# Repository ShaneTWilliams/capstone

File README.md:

# capstone

## Setup

First, clone submodules with:

```
git submodule update --init
cd software/firmware/lib/pico-sdk
git submodule update --init
```

You don't *have* to, but using a `venv` for the following steps is a good idea. To create one, run:

```
cd software
python -m venv .csvenv
```

Then to activate it, run the following. You'll need to do this each time you open a new shell, but you can put it in your shell's dotfile to automate this.

```
Bash:                   source .csvenv/bin/activate
Csh:                    source .csvenv/bin/activate.csh
Fish:                   source .csvenv/bin/activate.fish
Windows CMD:            .csvenv\Scripts\activate.bat
Windows PowerShell:     .csvenv\Scripts\Activate.ps1
```

### Windows

Open PowerShell as an administrator and install chocolatey using [these instructions](https://chocolatey.org/install#individual).

Still using an administrator shell, install dependencies with:

```
choco install make cmake mingw gcc-arm-embedded protoc python --installargs '"ADD_CMAKE_TO_PATH=User"'
```

In a non-administrator PowerShell, install the Python package with:

```
cd software
pip install -e . --user
```

If you get warnings about the scripts directory not being on your PATH, add it by typing `env` in the Windows search bar and click on "Edit the system environment variables". Next, on the `Advanced` tab, click `Environment Variables`. Under `User Variables`, find `Path`, click on it, select `Edit`, then click `New`. Type in the directory that Pip warned about, and exit.

Close and reopen your PowerShell window.

### Linux

Install dependencies with the following command:

```
sudo apt install cmake protobuf-compiler pnpm
```

Install the [GNU ARM embedded toolchain](https://developer.arm.com/downloads/-/arm-gnu-toolchain-downloads) manually.

Install the Python package with:

```
cd software
pip install -e .
```

If you get warnings about the scripts directory not being on your PATH, add it adding the following line to your shell's `rc` dotfile.

```
export PATH=$PATH:<scripts dir here>
```

### MacOS

Install dependencies with the following command:

```
brew install make cmake protobuf gcc-arm-embedded pnpm
```

Install the Python package with:

```
cd software
pip install -e .
```

If you get warnings about the scripts directory not being on your PATH, add it adding the following line to your shell's `rc` dotfile.

```
export PATH=$PATH:<scripts dir here>
```

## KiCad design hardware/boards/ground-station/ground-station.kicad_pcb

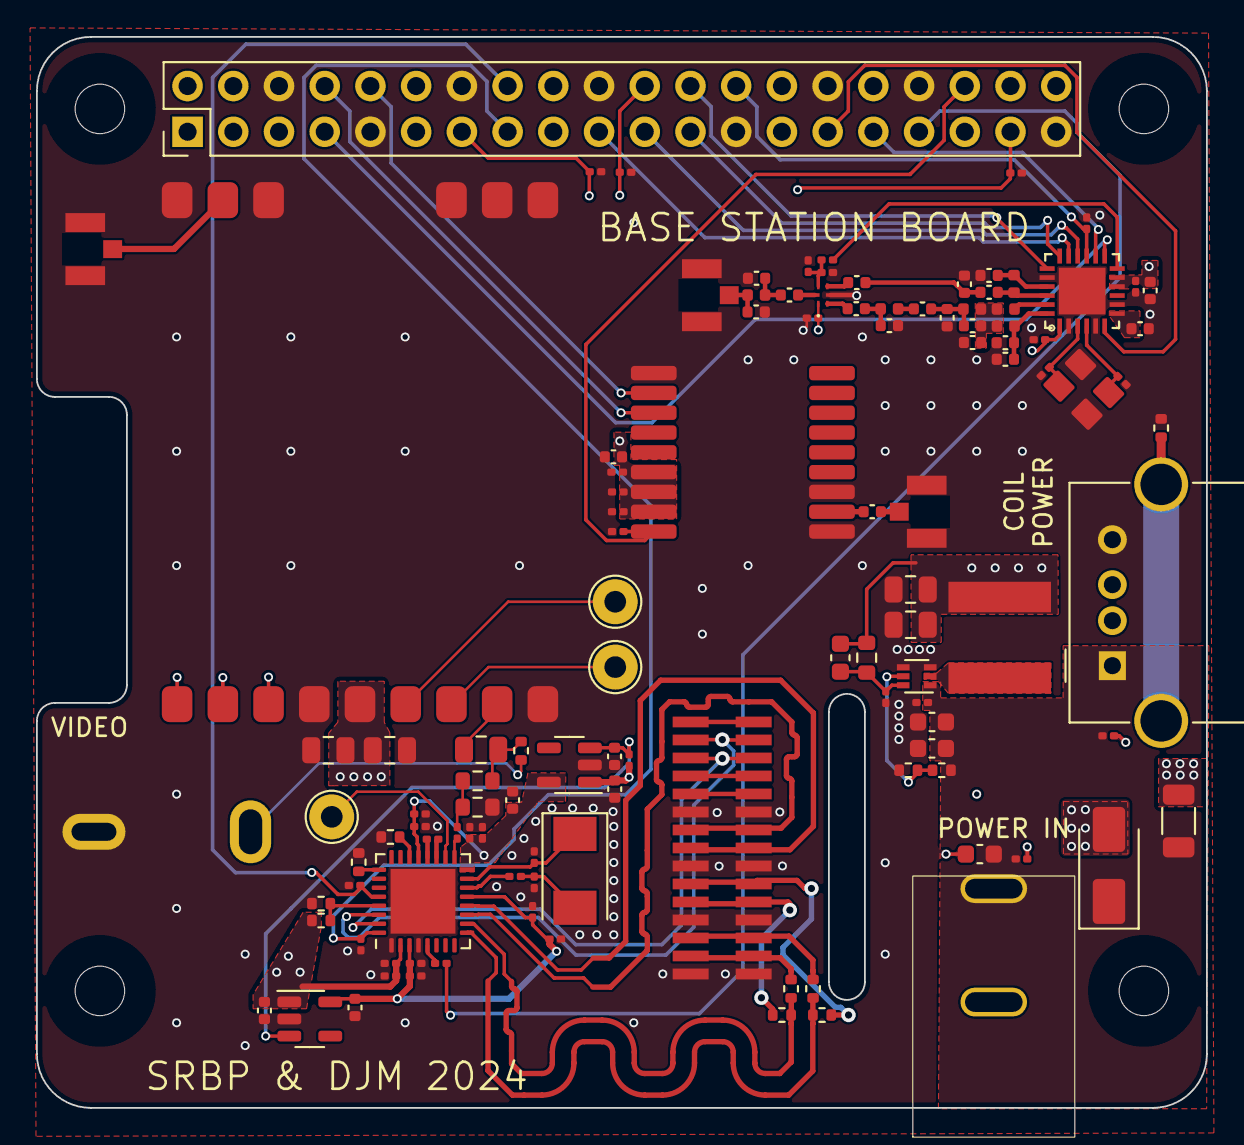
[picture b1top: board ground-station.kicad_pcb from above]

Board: 4 copper layers, 65.0 x 59.5 mm, 117 parts (0 on the bottom side), 77 nets.

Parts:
C1, C3, C24, C27, C205, C206, C207, C210, C231, C604, C611, C614, C615, C618, C620: 100n; C_0201_0603Metric
C2: C_0603_1608Metric
C23, C25, C26: 10u; C_0603_1608Metric
C33, C34, C201, C202, C203: 22u; C_0805_2012Metric
C204: 470n; C_0402_1005Metric
C208: 2.2u; C_0402_1005Metric
C209, C215: 47p; C_0402_1005Metric
C211, C605, C606, C607, C608: 1u; C_0402_1005Metric
C212, C214: 16p; C_0201_0603Metric
C213: 47n; C_0402_1005Metric
C216, C223: 1.8p; C_0402_1005Metric
C217: 2.4p; C_0402_1005Metric
C218, C224, C225: 1n; C_0402_1005Metric
C219, C221: 5.6p; C_0402_1005Metric
C220: 3p; C_0402_1005Metric
C222, C228: 39p; C_0402_1005Metric
C226: 100p; C_0201_0603Metric
C227, C612, C613, C616, C617, C619: 10n; C_0201_0603Metric
C229, C230: 3.3p; C_0402_1005Metric
C602, C603: 22p; C_0201_0603Metric
C610: 680n; C_0402_1005Metric
D401: SMAJ5.0A; D_SMA
J1: USB_A; USB_A_Molex_67643_Horizontal
J2: Barrel_Jack; PJ-037A
J3: Conn_Coaxial; RCJ-054
J101: Raspberry_Pi_2_3; PinHeader_2x20_P2.54mm_Vertical
J102: Conn_01x15; FFC3A20-15-G
J201, J202, J203: U.FL; U.FL-R-SMT-1(60)
L4: 1.5u; FNR6028S1R5MT
L201: 0R; L_0402_1005Metric
L202: 47n; L_0402_1005Metric
L203: 15n; L_0402_1005Metric
L204: 2.5n; L_0402_1005Metric
L205: 4.7n; L_0402_1005Metric
L206: 9.1n; L_0402_1005Metric
R1, R2, R6, R22, R23, R24, R25, R26, R27, R28, R208: 0; R_0402_1005Metric
R3: 0; R_1206_3216Metric
R4: 24R; R_0603_1608Metric
R5: 51R; R_0603_1608Metric
R7: 100k; R_0402_1005Metric
R8: 135k; R_0603_1608Metric
R9: 30k; R_0201_0603Metric
R201, R205, R604, R605: 100k; R_0201_0603Metric
R202, R203, R204, R606: 10k; R_0201_0603Metric
R206: 2.2k; R_0201_0603Metric
R207: 2.7k; R_0201_0603Metric
R301: 47R; R_0201_0603Metric
R603: 1k; R_0201_0603Metric
TP1, TP2, TP3: TestPoint; TestPoint_THTPad_D2.5mm_Drill1.2mm
U3: TPS564242DRLR; SOT-563
U201: SX1262IMLTRT
U202: RX5808
U203: SW-GPS01
U204: SKY13453-385LF; IC_SKY13453-385LF
U601: ADV7282A-M; QFN-32-1EP_5x5mm_P0.5mm_EP3.6x3.6mm
U602, U603: AP2127K-1.8; SOT-23-5
Y201: 32 MHz; JYJE-3TJ432000HYFBC
Y601: 28.63636 MHz; Crystal_SMD_Abracon_ABM3-2Pin_5.0x3.2mm

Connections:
+3V3: C2.2, C33.1, C34.1, C205.1, C206.1, C207.1, C208.1, C210.1, C211.1, C227.1, C231.1, C605.1, C606.1, C611.1, C612.1, L4.2, R8.1, R27.1, R606.1, U201.1 (VDD_IN), U201.10 (VBAT), U201.11 (VBAT_IO), U203.6 (V_BCKP), U203.7 (VCC_IO), U203.8 (VCC), U204.1 (VDD), U601.2 (DVDDIO), U602.1 (VIN), U603.1 (VIN)
+5V: C1.1, C23.1, C24.1, C25.1, C26.1, C27.1, C201.1, C202.1, D401.1 (A1), J1.1 (VBUS), J2.1, R2.1, R3.1, U3.1 (VIN), U202.5 (VCC)
/CAM_CK_N: J102.8, U601.12 (CLKN)
/CAM_CK_P: J102.9, U601.11 (CLKP)
/CAM_D0_CONN_N: J102.2, R25.2
/CAM_D0_CONN_P: J102.3, R26.2
/CAM_D0_N: R23.1, R25.1, U601.10 (D0N)
/CAM_D0_P: R24.1, R26.1, U601.9 (D0P)
/CAM_D1_CONN_N: J102.5, R23.2
/CAM_D1_CONN_P: J102.6, R24.2
/CAM_SCL: J102.13, U601.31 (SCLK)
/CAM_SDA: J102.14, U601.30 (SDATA)
/DIGITAL_RADIO_BUSY: J101.31 (GCLK2/GPIO6), U201.14 (BUSY)
/DIGITAL_RADIO_DIO1: J101.7 (GCLK0/GPIO4), U201.13 (DIO1)
/DIGITAL_RADIO_DIO3: J101.29 (GCLK1/GPIO5), U201.6 (DIO3)
/DIGITAL_RADIO_MISO: J101.21 (MISO0/GPIO9), U201.16 (MISO)
/DIGITAL_RADIO_MOSI: J101.19 (MOSI0/GPIO10), U201.17 (MOSI)
/DIGITAL_RADIO_SCLK: J101.23 (SCLK0/GPIO11), U201.18 (SCK)
/GPS_UART_RX: J101.8 (GPIO14/TXD), U203.3 (RXD)
/GPS_UART_TX: J101.10 (GPIO15/RXD), U203.2 (TXD)
/Radios/DIO2: R206.1, U201.12 (DIO2)
/Radios/SW_RX: C217.1, C218.2, C225.2
/Radios/SW_TX: C223.2, C224.2, L205.2
/Radios/VIDEO_OUT: C203.2, R4.1, R208.1
/Radios/XTAL_A: C214.1, U201.3 (XTA), Y201.1
/Radios/XTAL_B: C212.1, U201.4 (XTB), Y201.3
/VIDEO_CH1: J101.22 (GPIO25), R202.1, U202.9 (CH1)
/VIDEO_CH2: J101.37 (GPIO26), R203.1, U202.8 (CH2)
/VIDEO_CH3: J101.13 (GPIO27), R204.1, U202.7 (CH3)
/Video Digitizer/DIGITIZER_ANALOG_SUPPLY: C607.1, C617.1, C618.1, C619.1, C620.1, U601.16 (PVDD), U601.21 (AVDD), U603.5 (VOUT)
/Video Digitizer/DIGITIZER_DIGITAL_SUPPLY: C608.1, C613.1, C614.1, C615.1, C616.1, U601.3 (DVDD), U601.13 (MVDD), U602.5 (VOUT)
/Video Digitizer/VID_EN_1V8: C610.1, R606.2, U602.3 (EN), U603.3 (EN)
/~DIGITAL_RADIO_RESET: J101.26 (~CE1/GPIO7), R201.1, U201.15 (~NRESET)
/~DIGITAL_RADIO_nCS: J101.24 (~CE0/GPIO8), U201.19 (NSS)
/~DIGITIZER_INTRQ: J101.33 (PWM1/GPIO13), R301.2
/~DIGITIZER_PWRDWN: J101.15 (GPIO22), R604.1, U601.32 (~PWRDWN)
/~DIGITIZER_RESET: J101.16 (GPIO23), R605.1, U601.28 (~RESET)
/~GPS_RESET: J101.36 (GPIO16), R205.1, U203.9 (~RESET)
GND: C1.2, C23.2, C24.2, C25.2, C26.2, C27.2, C33.2, C34.2, C201.2, C202.2, C204.2, C205.2, C206.2, C207.2, C208.2, C210.2, C211.2, C212.2, C213.2, C214.2, C215.2, C216.2, C218.1, C219.2, C221.1, C223.1, C226.1, C227.2, C229.1, C230.1, C231.2, C602.1, C603.1, C605.2, C606.2, C607.2, C608.2, C610.2, C611.2, C612.2, C613.2, C614.2, C615.2, C616.2, C617.2, C618.2, C619.2, C620.2, D401.2 (A2), J1.4 (GND), J2.2, J3.2 (Ext), J101.6 (GND), J101.9 (GND), J101.14 (GND), J101.20 (GND), J101.25 (GND), J101.30 (GND), J101.34 (GND), J101.39 (GND), J102.1, J102.4, J102.7, J102.10, J201.2 (Ext), J202.2 (Ext), J203.2 (Ext), R1.2, R5.2, R6.1, R7.2, R9.2, R22.1, R28.1, R201.2, R202.2, R203.2, R204.2, R205.2, R207.1, R604.2, R605.2, U3.3 (GND), U3.4 (AGND), U201.2 (GND), U201.5 (GND), U201.8 (GND), U201.20 (GND), U201.25 (EXP), U202.1 (GND), U202.6 (GND), U202.10 (GND), U202.12 (GND), U202.13 (GND), U202.14 (GND), U202.15 (GND), U203.1 (GND), U203.10 (GND), U203.12 (GND), U204.3 (GND), U601.1 (DGND), U601.4 (DGND), U601.33 (EPAD), U602.2 (GND), U603.2 (GND), Y201.2, Y201.4
unnamed: C3.1, R4.2, R5.1
unnamed: C219.1, C220.1, L201.1, L202.1, L204.1
unnamed: C220.2, C221.2, C222.2, L204.2
unnamed: C222.1, L205.1
unnamed: C228.1, C229.2, L206.1
unnamed: C603.2, R603.1, Y601.2
unnamed: J1.5 (Shield), R1.1
unnamed: J3.1 (In), R208.2
unnamed: J101.2 (5V), J101.4 (5V), R3.2
unnamed: J201.1 (In), U202.11 (RFIN)
unnamed: C209.2, J202.1 (In)
unnamed: C230.2, J203.1 (In), L206.2
unnamed: R2.2, R7.1, U3.5 (EN)
unnamed: C2.1, R8.2, R9.1, U3.6 (FB)
unnamed: L4.1, U3.2 (SW)
unnamed: C217.2, L203.1, U201.22 (RFI_N)
unnamed: C216.1, L203.2, U201.21 (RFI_P)
unnamed: L201.2, U201.23 (RFO)
unnamed: C204.1, U201.7 (VREG)
unnamed: C213.1, C215.1, L202.2, U201.24 (VR_PA)
unnamed: TP2.1, U202.3 (AUDIO)
unnamed: TP1.1, U202.4 (RSSI)
unnamed: C203.1, U202.2 (VIDEO)
unnamed: C209.1, U203.11 (RF_IN)
unnamed: C224.1, U204.2 (RF1)
unnamed: C225.1, U204.4 (RF2)
unnamed: C228.2, U204.6 (RFC)
unnamed: C226.2, R206.2, R207.2, U204.5 (VTCL)
unnamed: C3.2, U601.17 (AIN1)
unnamed: TP3.1, U601.18 (AIN2)
unnamed: R27.2, R28.2, U601.29 (ALSB)
unnamed: R6.2, U601.22 (DIAG1)
unnamed: R22.2, U601.25 (DIAG2)
unnamed: C604.2, U601.20 (VREFN)
unnamed: C604.1, U601.19 (VREFP)
unnamed: C602.2, U601.15 (XTALN), Y601.1
unnamed: R603.2, U601.14 (XTALP)
unnamed: R301.1, U601.5 (~INTRQ)

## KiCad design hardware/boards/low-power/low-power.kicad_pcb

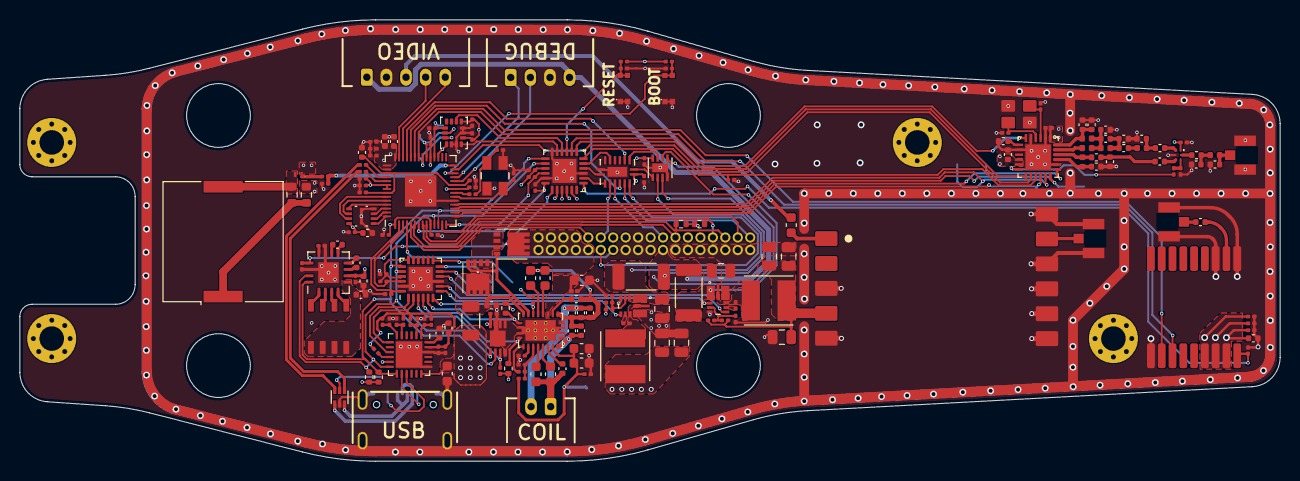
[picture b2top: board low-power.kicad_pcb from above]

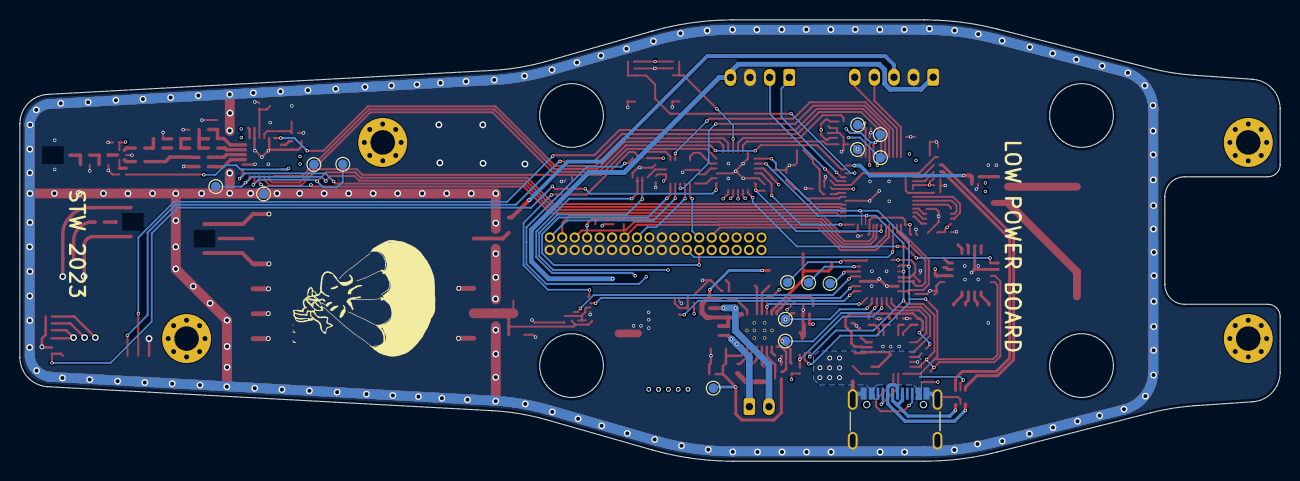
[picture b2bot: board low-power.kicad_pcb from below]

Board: 4 copper layers, 128.5 x 45.0 mm, 201 parts (18 on the bottom side), 156 nets.

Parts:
BZ801: Murata PKLCS; Buzzer_Murata_PKLCS1212E
C201, C202, C205, C209, C402, C502, C503, C504, C505, C506, C507, C510, C511, C512, C513, C514, C515, C517, C601, C602, C606, C607, C701, C702, C805, C806, C903, C904, C911, C1006: 100n; C_0201_0603Metric
C203, C501, C508, C509, C516, C804: 2.2u; C_0402_1005Metric
C204, C407: 47p; C_0402_1005Metric
C206, C207: 33nF; C_0402_1005Metric
C208: 68nF; C_0402_1005Metric
C210: 130p; C_0402_1005Metric
C211: 1uF; C_0402_1005Metric
C212: 1.8n; C_0402_1005Metric
C213, C218: 0.47uF; C_0603_1608Metric
C214, C217: 47nF; C_0603_1608Metric
C215, C216: 10nF; C_0402_1005Metric
C219, C220: 0.1uF; C_0201_0603Metric
C221, C222, C223: 10uF; C_0603_1608Metric
C301: 22u; C_0603_1608Metric
C302, C907, C908, C909, C910: 22u; C_0805_2012Metric
C401: 470n; C_0402_1005Metric
C403, C604, C605, C801, C802, C803: 1u; C_0402_1005Metric
C404, C406: 16p; C_0201_0603Metric
C405: 47n; C_0402_1005Metric
C408, C415: 1.8p; C_0402_1005Metric
C409: 2.4p; C_0402_1005Metric
C410, C416, C417: 1n; C_0402_1005Metric
C411, C413: 5.6p; C_0402_1005Metric
C412: 3p; C_0402_1005Metric
C414, C420: 39p; C_0402_1005Metric
C418: 1n; C_0201_0603Metric
C419: 10n; C_0201_0603Metric
C421, C422: 3.3p; C_0402_1005Metric
C518, C519: 30p; C_0201_0603Metric
C603: 1u; C_0603_1608Metric
C901, C902: 10u; C_0805_2012Metric
C905: 33p; C_0201_0603Metric
C906: 47p; C_0201_0603Metric
D601: USBLC6-2P6; SOT50P160X60-6N
D801: TC5050RGBW
H101, H102, H103, H104: MountingHole_Pad; MountingHole_2.5mm_Pad_Via
J101: Conn_01x05_Pin; JST_PH_S5B-PH-K_1x05_P2.00mm_Horizontal
J102: Conn_02x18_Top_Bottom; 20021311-00036T4LF
J103: Conn_01x04; JST_PH_S4B-PH-K_1x04_P2.00mm_Horizontal
J201, J301, J401: U.FL; U.FL-R-SMT-1(60)
J601: USB_C_Receptacle_USB2.0; USB_C_Receptacle_G-Switch_GT-USB-7010ASV
L201: TDK WR483265-15F5-G; JST_PH_S2B-PH-K_1x02_P2.00mm_Horizontal
L402: 0R; L_0402_1005Metric
L403: 47n; L_0402_1005Metric
L404: 15n; L_0402_1005Metric
L405: 2.5n; L_0402_1005Metric
L406: 4.7n; L_0402_1005Metric
L407: 9.1n; L_0402_1005Metric
L901: 4.7u; IND_LQH5BPN6R8NT0L
L902: 6.8u; IND_LQH5BPN6R8NT0L
Q201, Q202: DMP3013SFV; DMP3013SFV7
Q801: DMN2400UFB4; TRXDFN100X60X40-3N
R201, R401, R701, R801, R803: 100k; R_0201_0603Metric
R202, R206, R210, R501, R601, R602, R603, R1010, R1011: 10k; R_0201_0603Metric
R203: 0R; R_1206_3216Metric
R204: 66R; R_0201_0603Metric
R205: 196R; R_0201_0603Metric
R207, R208: 10k; R_0402_1005Metric
R209: 20k; R_0201_0603Metric
R402, R505: 100R; R_0201_0603Metric
R502, R503: 27R; R_0201_0603Metric
R504, R506, R507, R508: 4.7k; R_0402_1005Metric
R604: 4.7k; R_0201_0603Metric
R605, R606, R609, R610, R611, R612: 0R; R_0201_0603Metric
R607, R608: 5.1k; R_0201_0603Metric
R802: 7.5k; R_0201_0603Metric
R804: 1k; R_0201_0603Metric
R805: 330R; R_0603_1608Metric
R806: 1k; R_0603_1608Metric
R901, R902: 10m 1/2W; R_2010_5025Metric
R903: 91k; R_0201_0603Metric
R904, R906: 30k; R_0201_0603Metric
R905: 157k; R_0201_0603Metric
SW501, SW601: SW_Push; R-668048
TP202, TP203, TP204, TP505, TP506, TP507, TP508, TP509, TP510, TP511, TP512, TP1101, TP1102, TP1104: TestPoint; TestPoint_Pad_D1.0mm
U201: SW-GPS01
U202: LM75BTP,147
U203: BQ51013B; IC_MSP430FR2522IRHLR
U301: TX5813
U401: SX1262IMLTRT
U402: SKY13453-385LF; IC_SKY13453-385LF
U501: W25Q16JVUXIQ; IC_W25Q16JVUXIQ_TR
U502: RP2040; QFN-56-1EP_7x7mm_P0.4mm_EP3.2x3.2mm
U601, U1002: TCA9539RTWR; WQFN-24-1EP_4x4mm_P0.5mm_EP2.45x2.45mm
U602: TMUX1309BQBR; QFN50P350X250X80-17N
U603: CYPD3177; QFN-24-1EP_4x4mm_P0.5mm_EP2.7x2.7mm
U701: LSM6DSM; LGA-14_3x2.5mm_P0.5mm_LayoutBorder3x4y
U801: IS31FL3197; QFN-16-1EP_4x4mm_P0.65mm_EP2.1x2.1mm
U901, U902: AP63356QZV-7; CONV_AP63356QZV-7
U903: INA2180A3IDSGR; SON50P200X200X80-9N
Y401: 32 MHz; JYJE-3TJ432000HYFBC
Y501: 12 MHz; SMD_2MSB4SI_YXC

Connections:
+1V1: C502.1, C506.1, C509.1, U502.23 (DVDD), U502.45 (VREG_VOUT), U502.50 (DVDD)
+3V3: C201.1, C202.1, C203.1, C205.1, C209.1, C402.1, C403.1, C419.1, C501.1, C503.1, C504.1, C505.1, C507.1, C508.1, C510.1, C512.1, C513.1, C514.1, C515.1, C516.1, C517.1, C601.2, C602.1, C701.1, C702.1, C804.1, C805.1, C905.1, C907.1, C909.1, C911.1, C1006.2, J102.27, L901.2, R202.1, R207.1, R208.1, R210.1, R501.1, R504.1, R506.1, R507.1, R508.1, R602.1, R603.1, R805.1, R903.1, R1011.1, U201.6 (V_BCKP), U201.7 (VCC_IO), U201.8 (VCC), U202.8 (VCC), U401.1 (VDD_IN), U401.10 (VBAT), U401.11 (VBAT_IO), U402.1 (VDD), U501.8 (VCC), U502.1 (IOVDD), U502.10 (IOVDD), U502.22 (IOVDD), U502.33 (IOVDD), U502.42 (IOVDD), U502.43 (ADC_AVDD), U502.44 (VREG_IN), U502.48 (USB_VDD), U502.49 (IOVDD), U601.21 (VCC), U602.16 (VDD), U701.5 (VDDIO), U701.8 (VDD), U801.6 (VCC), U903.8 (VS), U1002.18 (A0), U1002.21 (VCC)
+5V: C302.1, C906.1, C908.1, C910.1, L902.2, R905.1, U301.4 (VCC)
+BATT: J101.1, J102.8, J103.4, R901.1, R902.1, U903.3 (IN1+), U903.5 (IN2+)
/33_PG: U902.5 (PG), U1002.7 (P06)
/50_EN: U901.2 (EN), U1002.8 (P07)
/50_PG: U901.5 (PG), U1002.10
/Charging/QI_EN1: R208.2, TP202.1, U203.10 (EN1), U1002.5 (P04)
/Charging/QI_EN2: R207.2, TP203.1, U203.11 (EN2), U1002.4 (P03)
/Charging/USB & USB-PD/USB-VBUS: C603.1, D601.5 (VP), J601.A4 (VBUS), J601.A9 (VBUS), J601.B4 (VBUS), J601.B9 (VBUS), R203.2, U603.11 (VDC_OUT), U603.18 (VBUS_IN)
/Charging/USB & USB-PD/USBPD_3V3: C605.1, C606.1, C607.1, R604.2, R605.1, R607.1, R609.1, R611.1, U603.23 (VDDD)
/Charging/USBPD_FAULT: U603.9 (FAULT), U1002.1 (P00)
/Charging/USB_D_N: D601.6 (L1), R502.1
/Charging/USB_D_P: D601.4 (L2), R503.1
/Charging/~CHG_IOX_INT: R1011.2, U502.3 (GPIO1), U1002.22 (~INT)
/Charging/~CHG_IOX_RST: R1010.1, U502.2 (GPIO0), U1002.24 (~RESET)
/Charging/~QI_CHG: R210.2, U203.7 (~CHG), U1002.6 (P05)
/Charging/~QI_TMP_OS: R202.2, U202.3 (OS), U1002.3 (P02)
/Charging/~USBPD_INT: U603.7 (HPI_INT), U1002.2 (P01)
/Digital Radio/BUSY: U401.14 (BUSY), U502.27 (GPIO16)
/Digital Radio/DIO1: U401.13 (DIO1), U601.13
/Digital Radio/DIO2: R402.1, U401.12 (DIO2)
/Digital Radio/DIO3: U401.6 (DIO3), U601.14
/Digital Radio/MISO: TP505.1, U401.16 (MISO), U502.15 (GPIO12)
/Digital Radio/MOSI: TP508.1, U401.17 (MOSI), U502.18 (GPIO15)
/Digital Radio/SCK: TP507.1, U401.18 (SCK), U502.17 (GPIO14)
/Digital Radio/SW_RX: C409.1, C410.2, C417.2
/Digital Radio/SW_TX: C415.2, C416.2, L406.2
/Digital Radio/XTAL_A: C406.1, U401.3 (XTA), Y401.1
/Digital Radio/XTAL_B: C404.1, U401.4 (XTB), Y401.3
/Digital Radio/~CS: TP506.1, U401.19 (NSS), U502.16 (GPIO13)
/Digital Radio/~RESET: R401.1, U401.15 (~NRESET), U601.12
/GPS/UART_RX: U201.3 (RXD), U502.36 (GPIO24)
/GPS/UART_TX: U201.2 (TXD), U502.37 (GPIO25)
/GPS/~RESET: R201.1, U201.9 (~RESET), U601.7 (P06)
/HP_SCL: J102.22, R508.2, U502.9 (GPIO7)
/HP_SDA: J102.21, R507.2, U502.8 (GPIO6)
/IMU/INT1: U601.17, U701.4 (INT1)
/IMU/INT2: U601.16, U701.9 (INT2)
/IMU/MISO: TP509.1, U502.31 (GPIO20), U701.1 (SDO/SA0)
/IMU/MOSI: TP512.1, U502.35 (GPIO23), U701.14 (SDA)
/IMU/SCK: TP511.1, U502.34 (GPIO22), U701.13 (SCL)
/IMU/~CS: R701.1, TP510.1, U502.32 (GPIO21), U701.12 (CS)
/Indication/BUZZ_CTRL: R803.1, R804.1, U502.28 (GPIO17)
/Indication/~LED_SHDN: R801.1, U601.1 (P00), U801.13 (SDB)
/LP_SCL: R506.2, U202.2 (SCL), U502.12 (GPIO9), U601.19 (SCL), U603.13 (HPI_SCL), U801.16 (SCL), U1002.19 (SCL)
/LP_SDA: R504.2, U202.1 (SDA), U502.11 (GPIO8), U601.20 (SDA), U603.12 (HPI_SDA), U801.15 (SDA), U1002.20 (SDA)
/LV Power/3V3_CS: U602.1 (S0B), U903.1 (OUT1)
/LV Power/3V3_CS-: C901.1, R901.2, U902.1 (VIN), U902.2 (EN), U903.2 (IN1-)
/LV Power/5V0_CS: U602.2 (S2B), U903.7 (OUT2)
/LV Power/5V0_CS-: C902.1, R902.2, U901.1 (VIN), U903.6 (IN2-)
/LV Power/SW_3V3: C904.2, L901.1, U902.7 (NC), U902.9 (SW)
/LV Power/SW_5V: C903.2, L902.1, U901.7 (NC), U901.9 (SW)
/MCU IO/AN_MUX_A0: U601.8 (P07), U602.10 (A0)
/MCU IO/AN_MUX_A1: U601.10, U602.9 (A1)
/MCU IO/LV_CS: U502.39 (GPIO27_ADC1), U602.3 (DB)
/MCU IO/MCU_BOOT: C806.1, R603.2, SW601.2, U601.15
/MCU IO/MOTOR_CS: U502.38 (GPIO26_ADC0), U602.13 (DA)
/MCU IO/~AN_MUX_EN: U601.11, U602.6 (~EN)
/MCU IO/~MISC_IOX_INT: R602.2, U502.14 (GPIO11), U601.22 (~INT)
/MCU IO/~MISC_IOX_RST: R601.1, U502.7 (GPIO5), U601.24 (~RESET)
/MCU/MCU_SWDCLK: J103.2, U502.24 (SWCLK)
/MCU/MCU_SWDIO: J103.1, U502.25 (SWD)
/MCU/MCU_XTAL_A: C518.1, U502.20 (XIN), Y501.1
/MCU/MCU_XTAL_B: R505.1, U502.21 (XOUT)
/MCU/QSPI_CLK: U501.6 (CLK), U502.52 (QSPI_SCLK)
/MCU/QSPI_IO0: U501.5 (IO0), U502.53 (QSPI_SD0)
/MCU/QSPI_IO1: U501.2 (IO1), U502.55 (QSPI_SD1)
/MCU/QSPI_IO2: U501.3 (IO2), U502.54 (QSPI_SD2)
/MCU/QSPI_IO3: U501.7 (IO3), U502.51 (QSPI_SD3)
/MCU/QSPI_~CS: U501.1 (~CS), U502.56 (QSPI_SS)
/MCU/RUN: C511.1, R501.2, SW501.2, U502.26 (RUN)
/MTR_FL_CS: J102.19, U602.14 (S1A)
/MTR_FL_SPEED: J102.20, U502.13 (GPIO10)
/MTR_FR_CS: J102.26, U602.12 (S0A)
/MTR_FR_SPEED: J102.25, U502.6 (GPIO4)
/MTR_RL_CS: J102.13, U602.15 (S2A)
/MTR_RL_SPEED: J102.12, U502.4 (GPIO2)
/MTR_RR_CS: J102.31, U602.11 (S3A)
/MTR_RR_SPEED: J102.32, U502.5 (GPIO3)
/VBUS: C219.1, C221.1, J102.14, J102.15, J102.16, J102.17, J102.18, J102.33, J102.34, J102.35, J102.36, Q202.1 (D), U203.4 (OUT)
/VIDEO_RX: J101.5, U502.40 (GPIO28_ADC2)
/VIDEO_TX: J101.4, U502.41 (GPIO29_ADC3)
/Video Radio/VIDEO: C301.2, J101.3
/~MTR_IOX_INT: J102.24, U601.4 (P03)
/~MTR_IOX_RST: J102.23, U601.5 (P04)
/~PWR_IOX_INT: J102.30, U601.2 (P01)
/~PWR_IOX_RST: J102.29, U601.3 (P02)
GND: C201.2, C202.2, C203.2, C205.2, C209.2, C211.2, C219.2, C220.2, C221.2, C222.2, C223.2, C302.2, C401.2, C402.2, C403.2, C404.2, C405.2, C406.2, C407.2, C408.2, C410.1, C411.2, C413.1, C415.1, C418.1, C419.2, C421.1, C422.1, C501.2, C502.2, C503.2, C504.2, C505.2, C506.2, C507.2, C508.2, C509.2, C510.2, C511.2, C512.2, C513.2, C514.2, C515.2, C516.2, C517.2, C518.2, C519.2, C601.1, C602.2, C603.2, C604.2, C605.2, C606.2, C607.2, C701.2, C702.2, C803.2, C804.2, C805.2, C806.2, C901.2, C902.2, C907.2, C908.2, C909.2, C910.2, C911.2, C1006.1, D601.2 (VN), J101.2, J102.1, J102.2, J102.3, J102.4, J102.5, J102.6, J102.7, J102.9, J102.10, J102.11, J102.28, J103.3, J201.2 (Ext), J301.2 (Ext), J401.2 (Ext), J601.A1 (GND), J601.A12 (GND), J601.B1 (GND), J601.B12 (GND), J601.S1 (SHIELD), Q801.2 (S), R201.2, R205.1, R206.2, R401.2, R601.2, R606.2, R608.2, R610.2, R612.2, R701.2, R801.2, R802.2, R803.2, R904.2, R906.2, R1010.2, SW501.1, SW601.1, U201.1 (GND), U201.10 (GND), U201.12 (GND), U202.4 (GND), U202.5 (A2), U202.6 (A1), U202.7 (A0), U202.9 (EP), U203.1 (PGND1), U203.20 (PGND2), U203.21 (PAD), U301.3 (PGND), U301.5 (PGND), U301.6 (CH1), U301.7 (CH2), U301.8 (CH3), U301.9 (AGND), U301.11 (AGND), U401.2 (GND), U401.5 (GND), U401.8 (GND), U401.20 (GND), U401.25 (EXP), U402.3 (GND), U501.4 (GND), U501.9 (EP), U502.19 (TESTEN), U502.57 (GND), U601.9 (GND), U601.18 (A0), U601.23 (A1), U601.25 (EP), U602.8 (GND), U602.17 (PAD), U603.19 (GND), U603.22 (VSS), U603.25 (EPAD), U701.2 (SDX), U701.3 (SCX), U701.6 (GND), U701.7 (GND), U801.11 (GND), U801.14 (AD), U801.17 (EP), U901.4 (COMP), U901.8 (GND), U902.4 (COMP), U902.8 (GND), U903.4 (GND), U903.9 (EP), U1002.9 (GND), U1002.23 (A1), U1002.25 (EP), Y401.2, Y401.4, Y501.2, Y501.4
unnamed: BZ801.2 (+), Q801.3 (D), R806.2
unnamed: BZ801.1 (-), R805.2, R806.1
unnamed: C206.1, C207.1, C208.1, L201.2
unnamed: C411.1, C412.1, L402.1, L403.1, L405.1
unnamed: C412.2, C413.2, C414.2, L405.2
unnamed: C414.1, L406.1
unnamed: C420.1, C421.2, L407.1
unnamed: C519.1, R505.2, Y501.3
unnamed: D601.1 (L1), J601.A7 (D-), J601.B7 (D-)
unnamed: D601.3 (L2), J601.A6 (D+), J601.B6 (D+)
unnamed: C803.1, D801.1 (RA), D801.2 (GA), D801.3 (BA), D801.4 (BA), U801.5 (VOUT)
unnamed: D801.7 (GK), U801.2 (OUT2)
unnamed: D801.8 (RK), U801.1 (OUT1)
unnamed: C204.2, J201.1 (In)
unnamed: J301.1 (In), U301.10 (ANT)
unnamed: C422.2, J401.1 (In), L407.2
unnamed: J601.A5 (CC1), U603.14 (CC2)
unnamed: J601.B5 (CC2), U603.15 (CC1)
unnamed: C211.1, Q201.1 (D), R203.1, U203.9 (AD)
unnamed: Q201.2 (G), Q202.2 (G), U203.8 (~AD_EN)
unnamed: Q201.3 (S), Q202.3 (S)
unnamed: Q801.1 (G), R804.2
unnamed: C204.1, U201.11 (RF_IN)
unnamed: C206.2, C207.2, C208.2, C210.2, C212.1, C213.1, C214.1, C215.1, U203.2 (AC1)
unnamed: C210.1, C212.2, C216.1, C217.1, C218.1, L201.1, U203.19 (AC2)
unnamed: C215.2, U203.3 (BOOT1)
unnamed: C216.2, U203.17 (BOOT2)
unnamed: C213.2, U203.5 (CLAMP1)
unnamed: C218.2, U203.16 (CLAMP2)
unnamed: C214.2, U203.6 (COMM1)
unnamed: C217.2, U203.15 (COMM2)
unnamed: R204.2, R205.2, R209.2, U203.14 (FOD)
unnamed: R204.1, U203.12 (ILIM)
unnamed: C220.1, C222.1, C223.1, R209.1, TP204.1, U203.18 (RECT)
unnamed: R206.1, U203.13 (TS/CTRL)
unnamed: C301.1, U301.1 (VIDEO)
unnamed: C409.2, L404.1, U401.22 (RFI_N)
unnamed: C408.1, L404.2, U401.21 (RFI_P)
unnamed: L402.2, U401.23 (RFO)
unnamed: C401.1, U401.7 (VREG)
unnamed: C405.1, C407.1, L403.2, U401.24 (VR_PA)
unnamed: C416.1, U402.2 (RF1)
unnamed: C417.1, U402.4 (RF2)
unnamed: C420.2, U402.6 (RFC)
unnamed: C418.2, R402.2, U402.5 (VTCL)
unnamed: R502.2, U502.46 (USB_DM)
unnamed: R503.2, U502.47 (USB_DP)
unnamed: R604.1, U603.10 (FLIP)
unnamed: R609.2, R610.1, U603.5 (ISINK_COARSE)
unnamed: R611.2, R612.1, U603.6 (ISINK_FINE)
unnamed: R607.2, R608.1, U603.2 (VBUS_MAX)
unnamed: R605.2, R606.1, U603.1 (VBUS_MIN)
unnamed: C604.1, U603.24 (VCCD)
unnamed: C801.2, U801.8 (C1N)
unnamed: C801.1, U801.7 (C1P)
unnamed: C802.2, U801.9 (C2N)
unnamed: C802.1, U801.10 (C2P)
unnamed: R802.1, U801.12 (ISET)
unnamed: D801.6 (BK), U801.3 (OUT3)
unnamed: D801.5 (BK), U801.4 (OUT4)
unnamed: C903.1, U901.6 (BST)
unnamed: C906.2, R905.2, R906.1, U901.3 (FB)
unnamed: C904.1, U902.6 (BST)
unnamed: C905.2, R903.2, R904.1, U902.3 (FB)
unnamed: TP1101.1, U1002.11
unnamed: TP1102.1, U1002.12
unnamed: TP1104.1, U1002.13
